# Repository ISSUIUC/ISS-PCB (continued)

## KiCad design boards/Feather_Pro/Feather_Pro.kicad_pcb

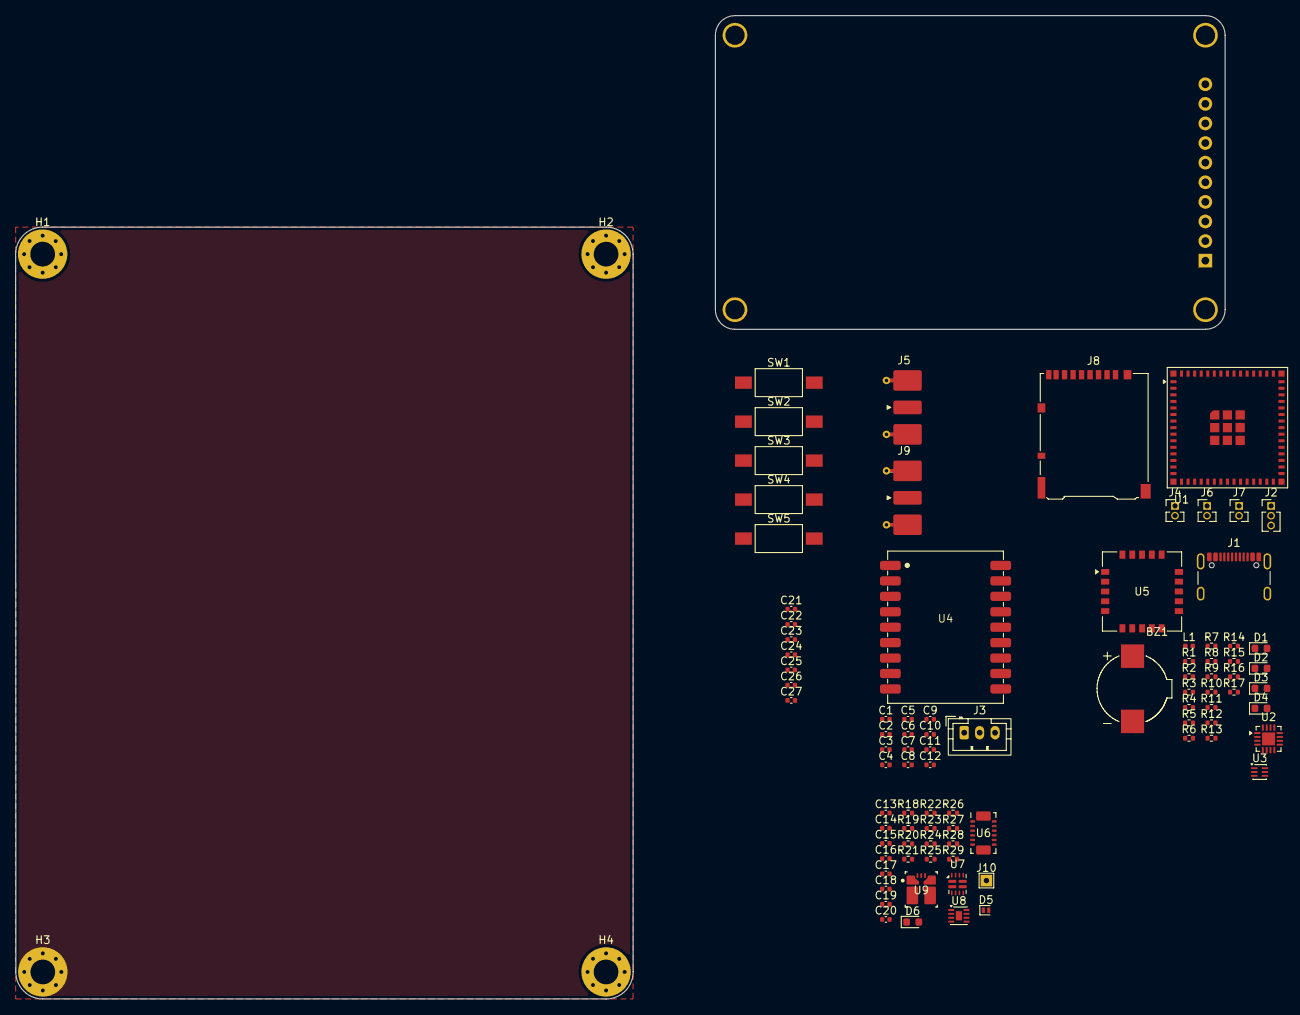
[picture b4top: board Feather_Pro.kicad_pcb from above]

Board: 4 copper layers, 156.7 x 127.4 mm, 93 parts (0 on the bottom side), 76 nets, no tracks yet.

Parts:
BZ1: Buzzer; Buzzer_SMTB-0927-TW-R
C1, C4, C5, C6, C7, C14, C26: 1uF; C_0402_1005Metric
C2, C20: 22uF; C_0402_1005Metric
C3, C13, C21, C22, C23, C24, C25: 0.1uF; C_0402_1005Metric
C8, C10, C17, C27: 100nF; C_0402_1005Metric
C9: 100pF; C_0402_1005Metric
C11: 10uF; C_0402_1005Metric
C12, C18: 10nF; C_0402_1005Metric
C15: 0.1 uF; C_0402_1005Metric
C16: 10Uf; C_0402_1005Metric
C19: 1 uF; C_0402_1005Metric
D1: RED LED; LED_0603_1608Metric
D2: ORANGE LED; LED_0603_1608Metric
D3: GREEN LED; LED_0603_1608Metric
D4: BLUE LED; LED_0603_1608Metric
D5: BAS116L; D_SOD-882
D6: LED; LED_0603_1608Metric
H1, H2, H3, H4: M3; MountingHole_3.2mm_M3_Pad_Via
J1: USB4105-GF-A; USB_C_Receptacle_GCT_USB4105-xx-A_16P_TopMnt_Horizontal
J2: Conn_01x03; PinHeader_1x03_P1.27mm_Vertical
J3: Conn_01x03; JST_PH_B3B-PH-K_1x03_P2.00mm_Vertical
J4, J6, J7: Conn_01x02; PinHeader_1x02_P1.27mm_Vertical
J5, J9: SMA; SMA_Molex_73251-2120_EdgeMount_Horizontal
J8: DM3AT-SF-PEJM5; microSD_HC_Hirose_DM3AT-SF-PEJM5
J10: TestPoint; TestPoint_THTPad_1.5x1.5mm_Drill0.7mm
L1: 330nH; L_0402_1005Metric
R1, R24, R27: 0; R_0402_1005Metric
R2, R17: 100k; R_0402_1005Metric
R3, R4, R5, R6, R29: 470; R_0402_1005Metric
R7, R8: 4.7k; R_0402_1005Metric
R9: 20k; R_0402_1005Metric
R10, R11: 5.1k; R_0402_1005Metric
R12, R13, R14, R15, R16, R22, R26: 10k; R_0402_1005Metric
R18, R20: 16.9k; R_0402_1005Metric
R19, R21: 5k; R_0402_1005Metric
R23: 21.5k; R_0402_1005Metric
R25: 11.8k; R_0402_1005Metric
R28: 10K; R_0402_1005Metric
SW1, SW2, SW3, SW4, SW5: SW_Push; SW_SPST_FSMSM
U1: ESP32-S3-MINI-1U; ESP32-S2-MINI-1U
U2: ADS7138-Q1; WQFN-16-1EP_3x3mm_P0.5mm_EP1.68x1.68mm
U3: ECMF02-2AMX6; ST_UQFN-6L_1.5x1.7mm_P0.5mm
U4: LR2021
U5: E22-400MM22S
U6: INA745x; VQFN-REL0014B
U7: TPS2121; Texas_VQFN-HR-12_2x2.5mm_P0.5mm
U8: MAX17048G+T10; TDFN-8-1EP_2x2mm_P0.5mm_EP0.8x1.2mm
U9: TPSM863253RDXR; QFN-FCMOD-RDX0007A
U10: LCD_2.2_in; Adafruit_2.2_LCD_SCREEN

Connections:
+3V3: C2.1, C3.1, C4.1, C5.1, C7.1, C8.1, C11.1, C12.1, C13.2, C20.1, C26.1, C27.1, J8.4 (VDD), R7.2, R8.2, R9.2, R12.2, R13.2, R14.2, R15.2, R16.2, R17.2, R22.1, R27.1, R28.1, R29.1, U1.3 (3V3), U2.7 (AVDD), U2.10 (DVDD), U4.1 (VCC), U5.1 (VCC), U6.3 (A1), U6.11 (VS), U9.3 (VOUT), U9.7 (FB), U10.9 (VIN)
/ADS_ALERT: U1.17 (IO13), U2.12 (ALERT)
/BOOT_SW: J3.1, U1.4 (IO0)
/BUTTON_CENTER: C25.2, SW5.2, U1.20 (IO16)
/BUTTON_DOWN: C22.1, SW2.1, U1.19 (IO15)
/BUTTON_LEFT: C24.2, SW4.2, U1.22 (IO18)
/BUTTON_RIGHT: C21.1, SW1.1, U1.21 (IO17)
/BUTTON_UP: C23.1, SW3.1, U1.18 (IO14)
/BUZZER: BZ1.1 (+), U2.15 (AIN0/GPIO0)
/D+: J1.A6 (D+), J1.B6 (D+), U3.6 (D+_out)
/D-: J1.A7 (D-), J1.B7 (D-), U3.5 (D-_out)
/E22_BUSY: U1.38 (IO42), U5.11 (BUSY)
/E22_CS: U1.16 (IO12), U5.14 (NSS)
/E22_DIO1: U1.36 (IO40), U5.20 (DIO1)
/E22_DIO3: U1.37 (IO41), U5.18 (DIO3)
/E22_RESET: C10.1, R17.1, U1.34 (IO38), U5.3 (NRST)
/E22_RXEN: U1.35 (IO39), U5.10 (RXEN)
/Feather_Pro_Power/PMUX_GND: C14.1, D5.2 (A), R19.2, R21.2, R23.1, U7.3 (CP2), U7.6 (PR1), U7.9 (ST), U7.12 (GND)
/GPIO_0: J7.1, U2.5 (AIN6/GPIO6)
/GPIO_1: J7.2, U2.6 (AIN7/GPIO7)
/I2C_SCL: J4.2, R8.1, U1.9 (IO5), U2.13 (SCL), U6.6 (SCL), U8.7 (SCL)
/I2C_SDA: J4.1, R7.1, U1.10 (IO6), U2.14 (SDA), U6.5 (SDA), U8.8 (SDA)
/INA_ALERT: R22.2, U1.30 (IO48), U6.10 (ALERT)
/LCD_BL: U1.27 (IO47), U10.1 (BL)
/LCD_CS: U1.15 (IO11), U10.5 (CS)
/LCD_D_C: U1.39 (TXD0), U10.8 (D/C)
/LCD_RST: U1.40 (RXD0), U10.7 (RST)
/LED_BLUE: R6.1, U2.3 (AIN4/GPIO4)
/LED_GREEN: R5.1, U2.2 (AIN3/GPIO3)
/LED_ORANGE: R4.1, U2.1 (ANI2/GPIO2)
/LED_RED: R3.1, U2.16 (AIN1/GPIO1)
/LR2021_ANT: C9.2, U4.9 (ANT)
/LR2021_BUSY: U1.28 (IO33), U4.7 (BUSY)
/LR2021_CS: U1.14 (IO10), U4.6 (~CS)
/LR2021_GPIO7: U1.25 (IO21), U4.17 (DIO7)
/LR2021_GPIO8: U1.5 (IO1), U4.16 (DIO8)
/LR2021_GPIO9: U1.6 (IO2), U4.15 (DIO9)
/LR2021_nRST: U1.8 (IO4), U4.14 (nRST)
/MAX_ALERT: R28.2, U2.4 (AIN5/GPIO5), U8.5 (*ALRT)
/MicroSD_CLK: J8.5 (CLK), U1.31 (IO35)
/MicroSD_CMD: J8.3 (CMD), R14.1, U1.32 (IO36)
/MicroSD_DAT0: J8.7 (DAT0), R13.1, U1.29 (IO34)
/RESET_SW: C6.1, J3.2, R9.1, U1.45 (EN)
/SPI_MISO: J2.3, U1.13 (IO9), U4.3 (MISO), U5.12 (MISO), U10.3 (MISO)
/SPI_MOSI: J2.2, U1.11 (IO7), U4.4 (MOSI), U5.13 (MOSI), U10.4 (MOSI)
/SPI_SCK: J2.1, U1.12 (IO8), U4.5 (SCK), U5.15 (SCK), U10.2 (SCK)
/SYS_POWER: J10.1 (Pin_1_1), U6.13 (VBUS), U6.14 (IS+), U7.1 (OUT), U7.8 (OUT)
/USB_D+: U1.24 (USB_D+), U3.1 (D+_in)
/USB_D-: U1.23 (USB_D-), U3.2 (D-_in)
/USB_POWER: J1.A4 (VBUS), J1.A9 (VBUS), J1.B4 (VBUS), J1.B9 (VBUS), R18.1, U7.7 (IN1)
/VBAT: C15.1, J6.1, R20.1, R24.1, U7.2 (IN2), U8.2 (CELL)
/VREG_IN: C16.1, C17.1, R25.1, U6.7 (IS-), U9.1 (VIN)
GND: BZ1.2 (-), C1.2, C2.2, C3.2, C4.2, C5.2, C6.2, C7.2, C8.2, C10.2, C11.2, C12.2, C13.1, C15.2, C16.2, C17.2, C18.2, C19.2, C20.2, C21.2, C22.2, C23.2, C24.1, C25.1, C26.2, C27.2, D1.1 (K), D2.1 (K), D3.1 (K), D4.1 (K), D5.1 (K), D6.1 (K), J1.A1 (GND), J1.A12 (GND), J1.B1 (GND), J1.B12 (GND), J3.3, J5.2 (Ext), J6.2, J8.6 (VSS), J9.2 (Ext), L1.2, R1.1, R10.2, R11.2, R26.2, SW1.2, SW2.2, SW3.2, SW4.1, SW5.1, U1.1 (GND), U1.2 (GND), U1.42 (GND), U1.43 (GND), U1.46 (GND), U1.47 (GND), U1.48 (GND), U1.49 (GND), U1.50 (GND), U1.51 (GND), U1.52 (GND), U1.53 (GND), U1.54 (GND), U1.55 (GND), U1.56 (GND), U1.57 (GND), U1.58 (GND), U1.59 (GND), U1.60 (GND), U1.61 (GND), U1.62 (GND), U1.63 (GND), U1.64 (GND), U1.65 (GND), U2.9 (GND), U2.17 (EPAD), U3.3 (GND), U4.2 (GND), U4.8 (GND), U4.11 (GND), U4.12 (GND), U4.18 (GND), U5.2 (GND), U5.7 (GND), U5.16 (GND), U6.4 (A0), U6.12 (GND), U8.1 (CTG), U8.4 (GND), U8.6 (QSTRT), U8.9 (EPAD), U9.4 (PGND), U10.10 (GND)
unnamed: D1.2 (A), R3.2
unnamed: D2.2 (A), R4.2
unnamed: D3.2 (A), R5.2
unnamed: D4.2 (A), R6.2
unnamed: D6.2 (A), R29.2
unnamed: J1.A5 (CC1), R10.1
unnamed: J1.B5 (CC2), R11.1
unnamed: C9.1, J5.1 (In)
unnamed: J8.8 (DAT1), R12.1
unnamed: J8.1 (DAT2), R16.1
unnamed: J8.2 (DAT3/CD), R15.1
unnamed: J9.1 (In), L1.1, U5.6 (ANT)
unnamed: R1.2, R2.2, U2.11 (ADDR)
unnamed: C1.1, R2.1, U2.8 (DECAP)
unnamed: U5.9 (TXEN), U5.19 (DIO2)
unnamed: U6.1 (SH+), U6.2 (IN+)
unnamed: U6.8 (SH-), U6.9 (IN-)
unnamed: R23.2, U7.10 (ILM)
unnamed: R18.2, R19.1, U7.5 (OV1)
unnamed: R20.2, R21.1, U7.4 (OV2)
unnamed: C14.2, U7.11 (SS)
unnamed: C19.1, R24.2, R27.2, U8.3 (VDD)
unnamed: C18.1, R25.2, R26.1, U9.6 (EN)

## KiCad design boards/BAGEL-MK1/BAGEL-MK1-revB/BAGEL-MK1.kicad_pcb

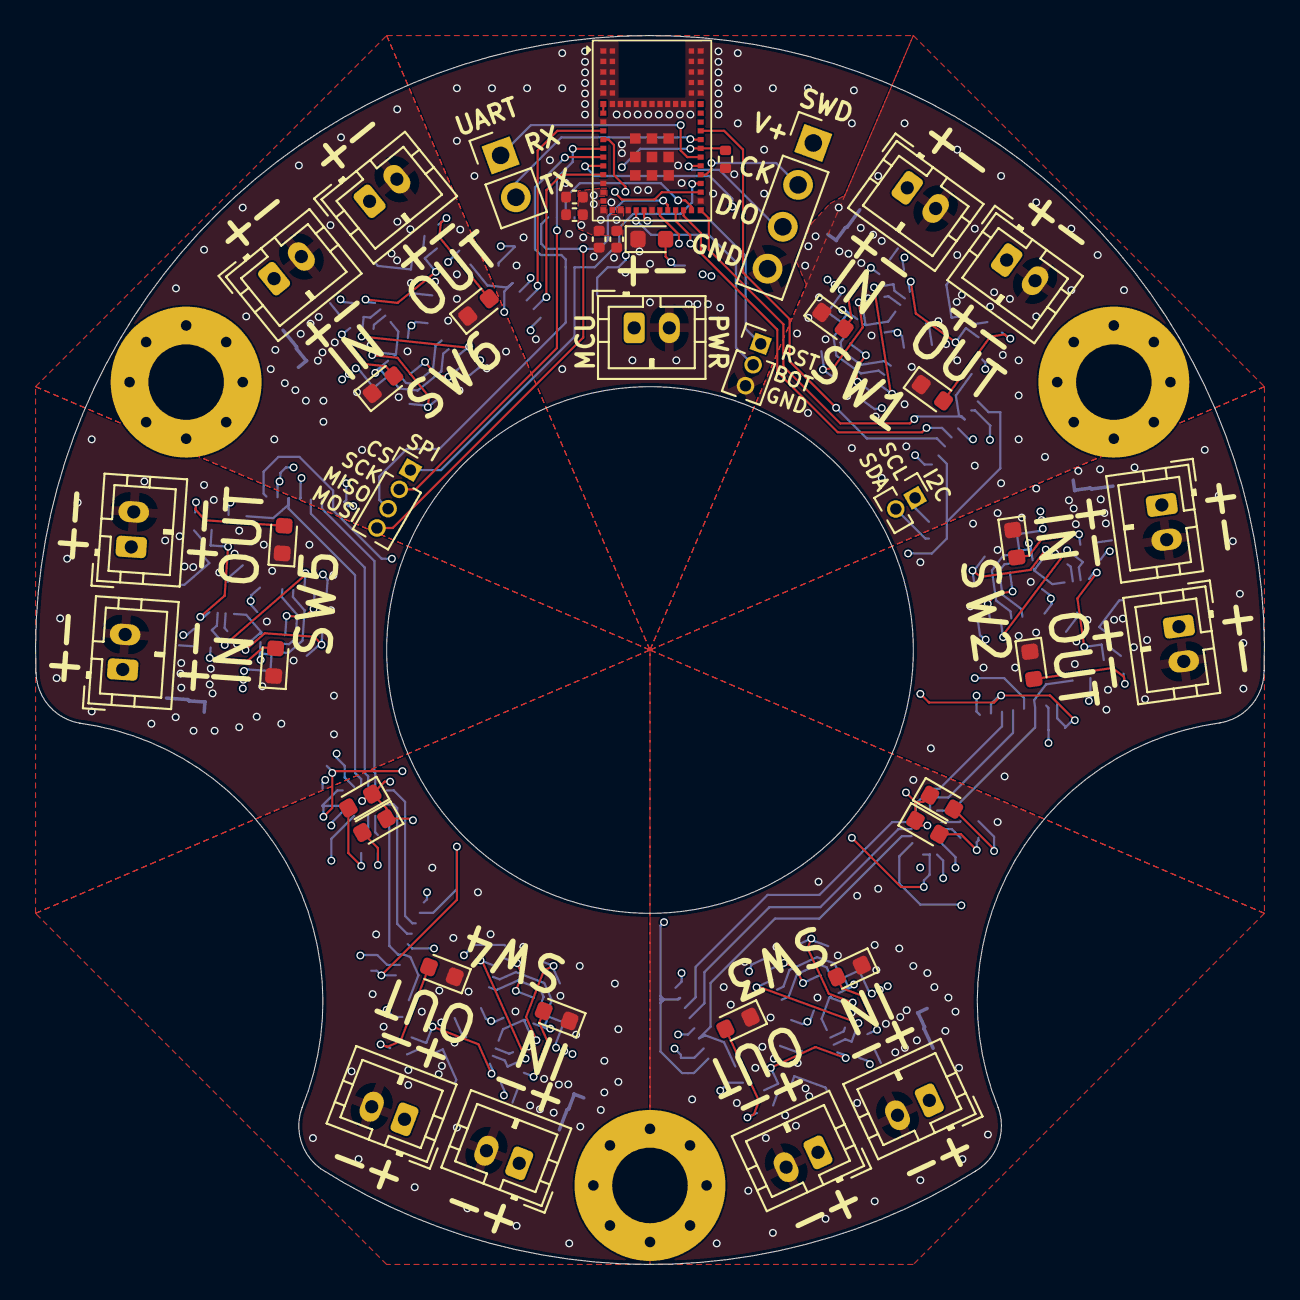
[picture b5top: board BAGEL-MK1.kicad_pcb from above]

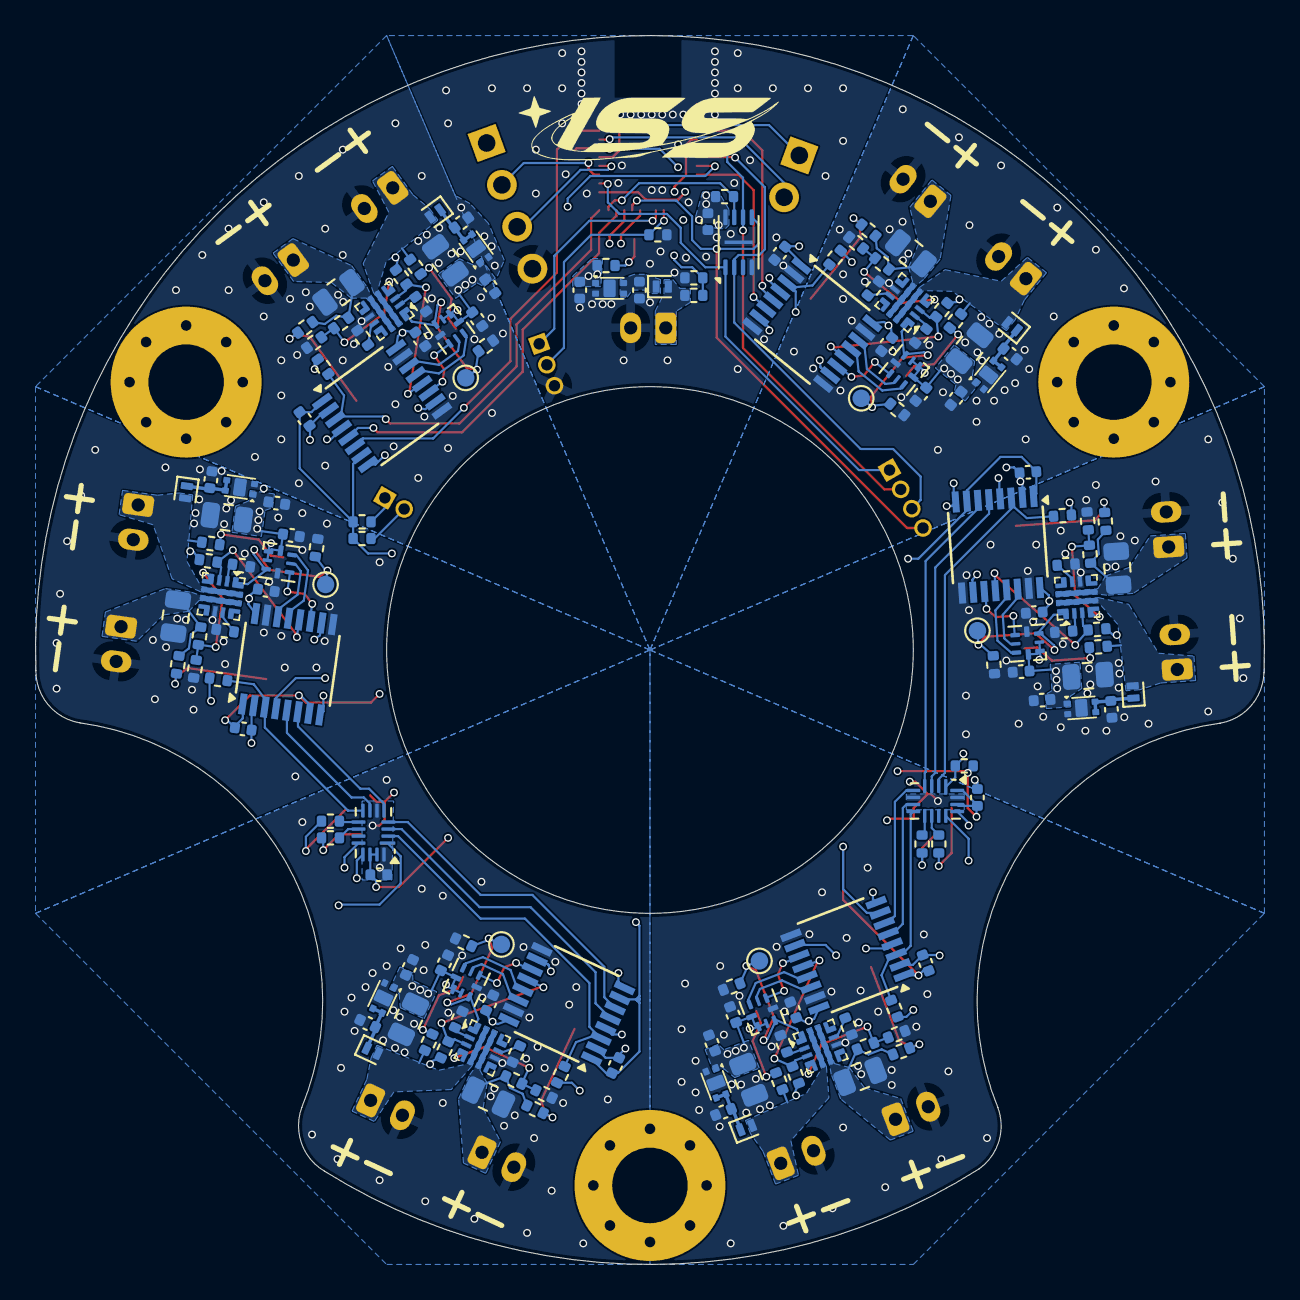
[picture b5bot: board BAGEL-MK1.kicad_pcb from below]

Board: 4 copper layers, 70.0 x 70.0 mm, 198 parts (154 on the bottom side), 138 nets.

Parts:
C101, C103, C104, C105, C108, C109, C201, C202, C203, C301, C302, C303, C401, C402, C403, C501, C502, C503, C601, C602, C603, C701, C702, C703: 100nF; C_0402_1005Metric
C102, C107: 4.7uF; C_0402_1005Metric
C106, C204, C205, C304, C305, C404, C405, C504, C505, C604, C605, C704, C705: 1uF; C_0402_1005Metric
C206, C306, C406, C506, C606, C706: 100uF; C_0805_2012Metric
C207, C307, C407, C507, C607, C707: 22uF; C_0805_2012Metric
D101, D201, D301, D401, D501, D601, D701: SDM05U40CSP-7; D_SOD-882
D102, D103, D202, D302, D402, D502, D602, D702: RED; LED_0603_1608Metric
D104: ORANGE; LED_0603_1608Metric
D105, D203, D303, D403, D503, D603, D703: GREEN; LED_0603_1608Metric
D106: BLUE; LED_0603_1608Metric
H101, H102, H103: MountingHole_Pad; MountingHole_4.3mm_M4_Pad_Via
J101: Conn_01x03; PinHeader_1x03_P1.27mm_Vertical
J102: Conn_01x04; PinHeader_1x04_P2.54mm_Vertical
J103, J201, J203, J301, J303, J401, J403, J501, J503, J601, J603, J701, J703: Conn_01x02; JST_PH_B2B-PH-K_1x02_P2.00mm_Vertical
J104: Conn_01x02; PinHeader_1x02_P2.54mm_Vertical
J105: Conn_01x02; PinHeader_1x02_P1.27mm_Vertical
J106: Conn_01x04; PinHeader_1x04_P1.27mm_Vertical
J202, J302, J402, J502, J602, J702: Conn_01x01; TestPoint_Pad_D1.0mm
R101, R102, R103, R113, R201, R202, R204, R301, R302, R304, R401, R402, R404, R501, R502, R504, R601, R602, R604, R701, R702, R704: 10k; R_0402_1005Metric
R104, R105, R106, R107, R108: 470; R_0402_1005Metric
R109, R112: 4.7k; R_0402_1005Metric
R110, R111: 100k; R_0402_1005Metric
R203, R209, R303, R309, R403, R409, R503, R509, R603, R609, R703, R709: 1k; R_0402_1005Metric
R205, R305, R405, R505, R605, R705: 680; R_0402_1005Metric
R206, R306, R406, R506, R606, R706: 390k; R_0402_1005Metric
R207, R307, R407, R507, R607, R707: 300k; R_0402_1005Metric
R208, R308, R408, R508, R608, R708: 500k; R_0402_1005Metric
U101: W25Q16JLUX; Winbond_USON-8-1EP_3x2mm_P0.5mm_EP0.2x1.6mm
U102: STM32WB1MMC; LGA77_6P5X10_STM
U103, U203, U303, U403, U503, U603, U703: XC6223; Torex_USP-4
U104, U105: TCAL9538; UQFN-16_1.8x2.6mm_P0.4mm
U201, U301, U401, U501, U601, U701: ISO7742; SSOP-16_3.9x4.9mm_P0.635mm
U202, U302, U402, U502, U602, U702: SN74AUP1G74RSER; UQFN-RSE0008A
U204, U304, U404, U504, U604, U704: TPS25947; VQFN-HR-RPW0010A

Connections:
/BLUE_LED: R108.1, U105.10 (P7)
/BOOT: J101.2, R102.2, U102.22 (BOOT0)
/CoinCell_V: D101.2 (A), J103.1, R110.2
/EXP_RESET: R103.1, U102.13 (PA2), U104.1 (~RESET), U105.1 (~RESET)
/FLASH_CS: J106.1, U101.1 (~CS), U102.33 (PB4)
/FLASH_RESET: R101.2, U101.7 (~HOLD/~RESET/IO_{3}), U102.29 (PA7)
/GPIO_Clock: R113.2, U102.37 (PA0), U201.4 (INB), U301.4 (INB), U401.4 (INB), U501.4 (INB), U601.4 (INB), U701.4 (INB)
/GREEN_LED: R107.1, U105.9 (P6)
/I2C_SCL: J105.1, R112.1, U102.27 (PB6), U104.12 (SCL), U105.12 (SCL)
/I2C_SDA: J105.2, R109.1, U102.25 (PB7), U104.13 (SDA), U105.13 (SDA)
/NRST: J101.1, U102.23 (NRST)
/ORANGE_LED: R106.1, U104.10 (P7)
/PG_ISO_1: U102.28 (PA3), U201.5 (OUTC)
/PG_ISO_2: U104.7 (P4), U301.5 (OUTC)
/PG_ISO_3: U104.3 (P1), U401.5 (OUTC)
/PG_ISO_4: U105.7 (P4), U501.5 (OUTC)
/PG_ISO_5: U105.3 (P1), U601.5 (OUTC)
/PG_ISO_6: U102.9 (PA4), U701.5 (OUTC)
/RED_LED: R105.1, U104.9 (P6)
/SPI_MISO: J106.3, U101.2 (DO/IO_{1}), U102.12 (PA6)
/SPI_MOSI: J106.4, U101.5 (DI/IO_{0}), U102.26 (PB5)
/SPI_SCK: J106.2, U101.6 (CLK), U102.11 (PA1)
/SWCLK: J102.2, U102.34 (PA14)
/SWDIO: J102.3, U102.35 (PA13)
/Switch 1/PG: R204.2, U201.12 (INC), U204.3 (PG/AUXOFF)
/Switch 1/Q: J202.1, R202.2, U202.3 (Q), U204.1 (EN/UVLO)
/Switch 1/Reg_V: C201.1, C203.1, C205.1, C206.1, R204.1, U201.10 (EN2), U201.16 (VCC2), U202.1 (~PRE), U202.2 (~CLR), U202.8 (VCC), U203.1 (VOUT)
/Switch 1/SubBatt_GND: C201.2, C203.2, C204.2, C205.2, C206.2, C207.2, D202.1 (K), D203.1 (K), J201.2, J203.2, R202.1, R205.1, R206.2, R208.2, U201.9 (GND2), U201.15 (GND2), U202.4 (GND), U203.2 (VSS), U203.5 (EP), U204.8 (GND)
/Switch 1/SubBatt_V: D201.2 (A), J201.1, R203.1, U204.5 (IN)
/Switch 1/~Q: U201.11 (IND), U202.5 (~Q)
/Switch 2/PG: R304.2, U301.12 (INC), U304.3 (PG/AUXOFF)
/Switch 2/Q: J302.1, R302.2, U302.3 (Q), U304.1 (EN/UVLO)
/Switch 2/Reg_V: C301.1, C303.1, C305.1, C306.1, R304.1, U301.10 (EN2), U301.16 (VCC2), U302.1 (~PRE), U302.2 (~CLR), U302.8 (VCC), U303.1 (VOUT)
/Switch 2/SubBatt_GND: C301.2, C303.2, C304.2, C305.2, C306.2, C307.2, D302.1 (K), D303.1 (K), J301.2, J303.2, R302.1, R305.1, R306.2, R308.2, U301.9 (GND2), U301.15 (GND2), U302.4 (GND), U303.2 (VSS), U303.5 (EP), U304.8 (GND)
/Switch 2/SubBatt_V: D301.2 (A), J301.1, R303.1, U304.5 (IN)
/Switch 2/~Q: U301.11 (IND), U302.5 (~Q)
/Switch 3/PG: R404.2, U401.12 (INC), U404.3 (PG/AUXOFF)
/Switch 3/Q: J402.1, R402.2, U402.3 (Q), U404.1 (EN/UVLO)
/Switch 3/Reg_V: C401.1, C403.1, C405.1, C406.1, R404.1, U401.10 (EN2), U401.16 (VCC2), U402.1 (~PRE), U402.2 (~CLR), U402.8 (VCC), U403.1 (VOUT)
/Switch 3/SubBatt_GND: C401.2, C403.2, C404.2, C405.2, C406.2, C407.2, D402.1 (K), D403.1 (K), J401.2, J403.2, R402.1, R405.1, R406.2, R408.2, U401.9 (GND2), U401.15 (GND2), U402.4 (GND), U403.2 (VSS), U403.5 (EP), U404.8 (GND)
/Switch 3/SubBatt_V: D401.2 (A), J401.1, R403.1, U404.5 (IN)
/Switch 3/~Q: U401.11 (IND), U402.5 (~Q)
/Switch 4/PG: R504.2, U501.12 (INC), U504.3 (PG/AUXOFF)
/Switch 4/Q: J502.1, R502.2, U502.3 (Q), U504.1 (EN/UVLO)
/Switch 4/Reg_V: C501.1, C503.1, C505.1, C506.1, R504.1, U501.10 (EN2), U501.16 (VCC2), U502.1 (~PRE), U502.2 (~CLR), U502.8 (VCC), U503.1 (VOUT)
/Switch 4/SubBatt_GND: C501.2, C503.2, C504.2, C505.2, C506.2, C507.2, D502.1 (K), D503.1 (K), J501.2, J503.2, R502.1, R505.1, R506.2, R508.2, U501.9 (GND2), U501.15 (GND2), U502.4 (GND), U503.2 (VSS), U503.5 (EP), U504.8 (GND)
/Switch 4/SubBatt_V: D501.2 (A), J501.1, R503.1, U504.5 (IN)
/Switch 4/~Q: U501.11 (IND), U502.5 (~Q)
/Switch 5/PG: R604.2, U601.12 (INC), U604.3 (PG/AUXOFF)
/Switch 5/Q: J602.1, R602.2, U602.3 (Q), U604.1 (EN/UVLO)
/Switch 5/Reg_V: C601.1, C603.1, C605.1, C606.1, R604.1, U601.10 (EN2), U601.16 (VCC2), U602.1 (~PRE), U602.2 (~CLR), U602.8 (VCC), U603.1 (VOUT)
/Switch 5/SubBatt_GND: C601.2, C603.2, C604.2, C605.2, C606.2, C607.2, D602.1 (K), D603.1 (K), J601.2, J603.2, R602.1, R605.1, R606.2, R608.2, U601.9 (GND2), U601.15 (GND2), U602.4 (GND), U603.2 (VSS), U603.5 (EP), U604.8 (GND)
/Switch 5/SubBatt_V: D601.2 (A), J601.1, R603.1, U604.5 (IN)
/Switch 5/~Q: U601.11 (IND), U602.5 (~Q)
/Switch 6/PG: R704.2, U701.12 (INC), U704.3 (PG/AUXOFF)
/Switch 6/Q: J702.1, R702.2, U702.3 (Q), U704.1 (EN/UVLO)
/Switch 6/Reg_V: C701.1, C703.1, C705.1, C706.1, R704.1, U701.10 (EN2), U701.16 (VCC2), U702.1 (~PRE), U702.2 (~CLR), U702.8 (VCC), U703.1 (VOUT)
/Switch 6/SubBatt_GND: C701.2, C703.2, C704.2, C705.2, C706.2, C707.2, D702.1 (K), D703.1 (K), J701.2, J703.2, R702.1, R705.1, R706.2, R708.2, U701.9 (GND2), U701.15 (GND2), U702.4 (GND), U703.2 (VSS), U703.5 (EP), U704.8 (GND)
/Switch 6/SubBatt_V: D701.2 (A), J701.1, R703.1, U704.5 (IN)
/Switch 6/~Q: U701.11 (IND), U702.5 (~Q)
/Switch_1: R201.1, U102.30 (PA12), U201.3 (INA)
/Switch_2: R301.1, U104.8 (P5), U301.3 (INA)
/Switch_3: R401.1, U104.2 (P0), U401.3 (INA)
/Switch_4: R501.1, U105.8 (P5), U501.3 (INA)
/Switch_5: R601.1, U105.2 (P0), U601.3 (INA)
/Switch_6: R701.1, U102.32 (PA11), U701.3 (INA)
/UART_RX: J104.1, U102.36 (PA10)
/UART_TX: J104.2, U102.38 (PA9)
/V_SENSE: R110.1, R111.2, U102.10 (PA8)
/~Q_ISO_1: U102.39 (PA5), U201.6 (OUTD)
/~Q_ISO_2: U104.5 (P3), U301.6 (OUTD)
/~Q_ISO_3: U104.4 (P2), U401.6 (OUTD)
/~Q_ISO_4: U105.5 (P3), U501.6 (OUTD)
/~Q_ISO_5: U105.4 (P2), U601.6 (OUTD)
/~Q_ISO_6: U102.14 (PB8), U701.6 (OUTD)
MCU_GND: C101.2, C102.2, C103.2, C104.2, C105.2, C106.2, C107.2, C108.2, C109.2, C202.2, C302.2, C402.2, C502.2, C602.2, C702.2, D102.1 (K), D103.1 (K), D104.1 (K), D105.1 (K), D106.1 (K), J101.3, J102.4, J103.2, R102.1, R111.1, R113.1, R201.2, R301.2, R401.2, R501.2, R601.2, R701.2, U101.4 (GND), U101.9 (EP), U102.1 (VSS), U102.2 (VSS), U102.3 (VSS), U102.4 (VSS), U102.5 (VSSRF), U102.8 (VSSRF), U102.15 (VSS), U102.17 (VSS), U102.19 (VSS), U102.21 (VSSSMPS), U102.24 (VSS), U102.31 (VSS), U102.43 (VSS), U102.44 (VSS), U102.45 (VSS), U102.46 (VSS), U102.47 (VSS), U102.48 (VSS), U102.49 (VSS), U102.50 (VSS), U102.51 (VSS), U102.52 (VSS), U102.53 (VSS), U102.54 (VSS), U102.55 (VSS), U102.56 (VSS), U102.57 (VSS), U102.58 (VSS), U102.59 (VSS), U102.60 (VSS), U102.61 (VSS), U102.62 (VSS), U102.63 (VSS), U102.64 (VSS), U102.65 (VSS), U102.66 (VSS), U102.67 (VSS), U102.68 (VSS), U102.69 (VSS), U102.70 (VSS), U102.71 (VSS), U102.72 (VSS), U102.73 (VSS), U102.74 (VSS), U102.75 (VSS), U102.76 (VSS), U102.77 (VSS), U103.2 (VSS), U103.5 (EP), U104.6 (GND), U104.16 (A1), U105.6 (GND), U105.15 (A0), U201.2 (GND1), U201.8 (GND1), U301.2 (GND1), U301.8 (GND1), U401.2 (GND1), U401.8 (GND1), U501.2 (GND1), U501.8 (GND1), U601.2 (GND1), U601.8 (GND1), U701.2 (GND1), U701.8 (GND1)
MCU_V: C101.1, C102.1, C103.1, C104.1, C105.1, C107.1, C108.1, C109.1, C202.1, C302.1, C402.1, C502.1, C602.1, C702.1, J102.1, R101.1, R103.2, R104.2, R109.2, R112.2, U101.8 (VCC), U102.16 (VDDA), U102.18 (VBAT), U102.20 (VDDSMPS), U103.1 (VOUT), U104.14 (VCC), U104.15 (A0), U105.14 (VCC), U105.16 (A1), U201.1 (VCC1), U201.7 (EN1), U301.1 (VCC1), U301.7 (EN1), U401.1 (VCC1), U401.7 (EN1), U501.1 (VCC1), U501.7 (EN1), U601.1 (VCC1), U601.7 (EN1), U701.1 (VCC1), U701.7 (EN1)
unnamed: C106.1, D101.1 (K), U103.3 (CE), U103.4 (VIN)
unnamed: D102.2 (A), R104.1
unnamed: D103.2 (A), R105.2
unnamed: D104.2 (A), R106.2
unnamed: D105.2 (A), R107.2
unnamed: D106.2 (A), R108.2
unnamed: C204.1, D201.1 (K), U203.3 (CE), U203.4 (VIN)
unnamed: D202.2 (A), R203.2
unnamed: D203.2 (A), R209.2
unnamed: C304.1, D301.1 (K), U303.3 (CE), U303.4 (VIN)
unnamed: D302.2 (A), R303.2
unnamed: D303.2 (A), R309.2
unnamed: C404.1, D401.1 (K), U403.3 (CE), U403.4 (VIN)
unnamed: D402.2 (A), R403.2
unnamed: D403.2 (A), R409.2
unnamed: C504.1, D501.1 (K), U503.3 (CE), U503.4 (VIN)
unnamed: D502.2 (A), R503.2
unnamed: D503.2 (A), R509.2
unnamed: C604.1, D601.1 (K), U603.3 (CE), U603.4 (VIN)
unnamed: D602.2 (A), R603.2
unnamed: D603.2 (A), R609.2
unnamed: C704.1, D701.1 (K), U703.3 (CE), U703.4 (VIN)
unnamed: D702.2 (A), R703.2
unnamed: D703.2 (A), R709.2
unnamed: C207.1, J203.1, R207.1, R209.1, U204.6 (OUT)
unnamed: C307.1, J303.1, R307.1, R309.1, U304.6 (OUT)
unnamed: C407.1, J403.1, R407.1, R409.1, U404.6 (OUT)
unnamed: C507.1, J503.1, R507.1, R509.1, U504.6 (OUT)
unnamed: C607.1, J603.1, R607.1, R609.1, U604.6 (OUT)
unnamed: C707.1, J703.1, R707.1, R709.1, U704.6 (OUT)
unnamed: U102.6 (ANT_IN), U102.7 (ANT_OUT)
unnamed: U201.14 (OUTA), U202.6 (D)
unnamed: U201.13 (OUTB), U202.7 (CLK)
unnamed: R205.2, U204.9 (ILM)
unnamed: R206.1, U204.2 (OVLO/OVCSEL)
unnamed: R207.2, R208.1, U204.4 (PGTH/NFLT)
unnamed: U301.14 (OUTA), U302.6 (D)
unnamed: U301.13 (OUTB), U302.7 (CLK)
unnamed: R305.2, U304.9 (ILM)
unnamed: R306.1, U304.2 (OVLO/OVCSEL)
unnamed: R307.2, R308.1, U304.4 (PGTH/NFLT)
unnamed: U401.14 (OUTA), U402.6 (D)
unnamed: U401.13 (OUTB), U402.7 (CLK)
unnamed: R405.2, U404.9 (ILM)
unnamed: R406.1, U404.2 (OVLO/OVCSEL)
unnamed: R407.2, R408.1, U404.4 (PGTH/NFLT)
unnamed: U501.14 (OUTA), U502.6 (D)
unnamed: U501.13 (OUTB), U502.7 (CLK)
unnamed: R505.2, U504.9 (ILM)
unnamed: R506.1, U504.2 (OVLO/OVCSEL)
unnamed: R507.2, R508.1, U504.4 (PGTH/NFLT)
unnamed: U601.14 (OUTA), U602.6 (D)
unnamed: U601.13 (OUTB), U602.7 (CLK)
unnamed: R605.2, U604.9 (ILM)
unnamed: R606.1, U604.2 (OVLO/OVCSEL)
unnamed: R607.2, R608.1, U604.4 (PGTH/NFLT)
unnamed: U701.14 (OUTA), U702.6 (D)
unnamed: U701.13 (OUTB), U702.7 (CLK)
unnamed: R705.2, U704.9 (ILM)
unnamed: R706.1, U704.2 (OVLO/OVCSEL)
unnamed: R707.2, R708.1, U704.4 (PGTH/NFLT)

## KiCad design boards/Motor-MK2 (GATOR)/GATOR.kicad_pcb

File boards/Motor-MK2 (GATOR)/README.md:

# Motorboard MK2 - GATOR

G - Grounded 

A - Arieal 

T - Tracker 

O - for Our 

R - Rocket 

# MK2

MK2 now includes an onboard LoRa reciever and GPS, removing the need for another MIDAS to act as a ground station.
It now also includes Qwiic connectors for additional I2C support and an IMU for orientation correction if needed.

# MK1

Starting off the year as just a concept, the Motor Board has taken shape as an impressive new piece of the MIDAS ecosystem. Unofficially known as “Spinny Antenna Motor” (SAM) Board, the project serves as a method of control for the team’s SAM Turret antenna tracker, which aims to automatically track the rocket’s position during flight and maintain optimal antenna orientation to get the best possible range for MIDAS telemetry. In addition to cementing MIDAS’s role as an important part of our team’s ground operations, the Motor Board has served as a testbed for WiFi as a new way of board-to-board communication.

Read more about MotorBoard, MIDAS and the surrounding avionics systems in the [MIDAS MK2 Report](https://uofi.box.com/s/k0ad6ryhxbzwpdwt33lxyxuxpivv3qhj).

# Schematics

Printable PDF schematics and layouts for MotorBoard can be found in the PDFs and images folders.

# Photos

## MK1

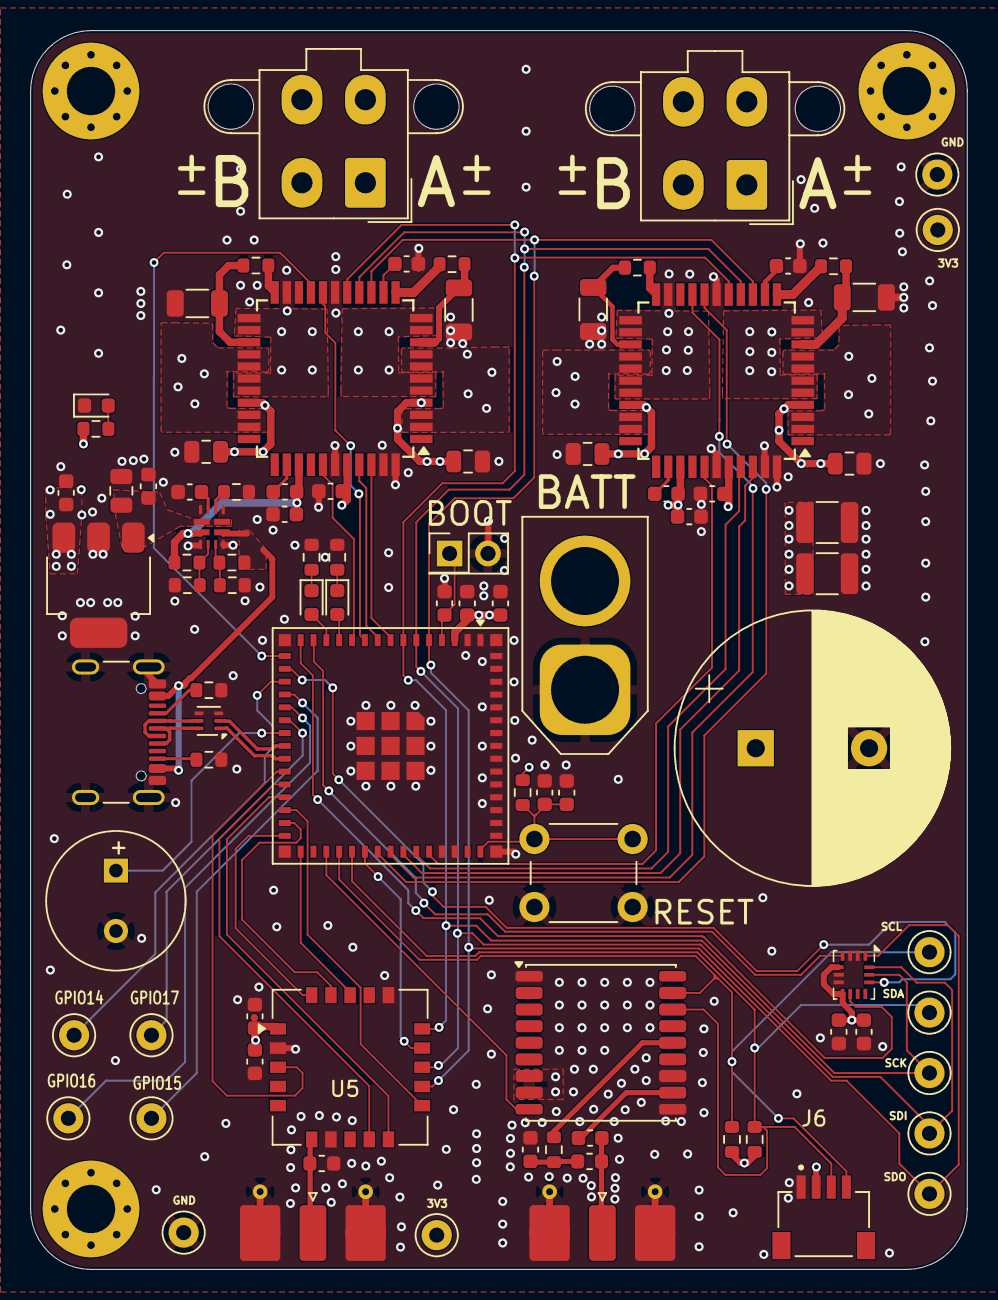
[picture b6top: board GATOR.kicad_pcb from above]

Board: 4 copper layers, 62.0 x 82.0 mm, 92 parts (0 on the bottom side), 79 nets.

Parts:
BZ1: AT-0927-TT-6-R; Buzzer_AT-0927-TT-6-R
C1, C3, C8, C10, C14, C16, C18, C25: 100nF; C_0603_1608Metric
C2, C12: 220nF; C_0603_1608Metric
C4, C5, C17, C19, C26: 10uF; C_0805_2012Metric
C6, C27: 22uF; C_0603_1608Metric
C7, C20: 470nF; C_0603_1608Metric
C9: 1200uF; CP_Radial_D18.0mm_P7.50mm
C11, C23: 1uF; C_0603_1608Metric
C13, C15: 100uF; C_1210_3225Metric
C21: 10uF; C_0603_1608Metric
C22, C402: 10nF; C_0603_1608Metric
C102, C103: 0.1uF; C_0603_1608Metric
C403: 47pF; C_0603_1608Metric
D1, D2: LED; LED_0603_1608Metric
D3: RED LED; LED_0603_1608Metric
H1, H2, H3: MountingHole; MountingHole_3.2mm_M3_Pad_Via
J1: USB_C_Receptacle_USB2.0_16P; USB_C_Receptacle_GCT_USB4105-xx-A_16P_TopMnt_Horizontal
J2, J4: Conn_01x04; Molex_Mini-Fit_Jr_5566-04A2_2x02_P4.20mm_Vertical
J3: XT60; AMASS_XT60-M_1x02_P7.20mm_Vertical
J5, J401: SMA; SMA_Molex_73251-2120_EdgeMount_Horizontal
J6: PRT-14417; Qwiic_4_pin_horizontal
L1: 330nH; L_0603_1608Metric
L401: 27nH; L_0603_1608Metric
R1, R2: 5.1k; R_0603_1608Metric
R3, R4, R8, R9, R401: 10; R_0603_1608Metric
R5, R6, R10, R11: 0.075; R_1206_3216Metric
R7: 100k; R_0603_1608Metric
R12: 23.7k; R_0603_1608Metric
R13: 5k; R_0603_1608Metric
R14: 30k; R_0603_1608Metric
R15: 1k; R_0603_1608Metric
R16, R17, R21: 470; R_0603_1608Metric
R18: 20k; R_0603_1608Metric
R19, R20: 4.7k; R_0603_1608Metric
SW1: SW_Push; PinHeader_2x01_P2.54mm_Vertical
SW2: SW_Push; SW_PUSH_6mm
TP3V3-1, TP3V3-2: 3V3; TestPoint_Keystone_5000-5004_Miniature
TP-GND-1, TP-GND-2: GND; TestPoint_Keystone_5000-5004_Miniature
TP-IO14-1: GPIO14; TestPoint_Keystone_5000-5004_Miniature
TP-IO15-2: GPIO15; TestPoint_Keystone_5000-5004_Miniature
TP-IO16-3: GPIO16; TestPoint_Keystone_5000-5004_Miniature
TP-IO17-4: GPIO17; TestPoint_Keystone_5000-5004_Miniature
TPSCK1: SCK; TestPoint_Keystone_5000-5004_Miniature
TPSCL1: I2C_SCL; TestPoint_Keystone_5000-5004_Miniature
TPSDA1: I2C_SDA; TestPoint_Keystone_5000-5004_Miniature
TPSDI1: SDI; TestPoint_Keystone_5000-5004_Miniature
TPSDO1: SDO; TestPoint_Keystone_5000-5004_Miniature
U1, U4: TMC2660C; TQFP-44_10x10mm_P0.8mm
U2: ESP32-S3-MINI-1U; ESP32-S2-MINI-1U
U3: ECMF02-2AMX6; ST_UQFN-6L_1.5x1.7mm_P0.5mm
U5: E22-400MM22S
U6: TPS2121; VQFN-HR-RUX0012A
U8: TLE42744; SOT-223
U102: LSM6DSLTR; Bosch_LGA-14_3x2.5mm_P0.5mm
U403: MAX-M10S; ublox_MAX

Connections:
+3V3: C1.2, C6.2, C8.2, C10.2, C21.1, C22.1, C27.1, C102.1, C103.1, J6.2, R7.1, R19.2, R20.2, R21.1, TP3V3-1.1, TP3V3-2.1, U1.40 (VCC_IO), U2.3 (3V3), U4.40 (VCC_IO), U5.1 (VCC), U8.3 (Q), U102.5 (VDDIO), U102.8 (VDD), U403.7 (VCC_IO), U403.8 (VCC)
/BUZZER: BZ1.1 (-), U2.22 (IO18)
/D+: J1.A6 (D+), J1.B6 (D+), U3.6 (D+_out)
/D-: J1.A7 (D-), J1.B7 (D-), U3.5 (D-_out)
/DIR_0: U1.41 (DIR), U2.9 (IO5)
/DIR_1: U2.40 (RXD0), U4.41 (DIR)
/E22_BUSY: U2.28 (IO33), U5.11 (BUSY)
/E22_DI01: U2.30 (IO48), U5.20 (DIO1)
/E22_DI02: U2.29 (IO34), U5.19 (DIO2)
/E22_DI03: U2.31 (IO35), U5.18 (DIO3)
/E22_RESET: U2.25 (IO21), U5.3 (NRST)
/GPIO14: TP-IO14-1.1, U2.18 (IO14)
/GPIO15: TP-IO15-2.1, U2.19 (IO15)
/GPIO16: TP-IO16-3.1, U2.20 (IO16)
/GPIO17: TP-IO17-4.1, U2.21 (IO17)
/I2C_SCL: J6.4, R19.1, TPSCL1.1, U2.34 (IO38), U403.17 (SCL)
/I2C_SDA: J6.3, R20.1, TPSDA1.1, U2.35 (IO39), U403.16 (SDA)
/LED_1: D1.2 (A), U2.12 (IO8)
/LED_2: D2.2 (A), U2.13 (IO9)
/LORA_CS: U2.36 (IO40), U5.14 (NSS)
/LSM6DSLTR_INT1: U2.14 (IO10), U102.4 (INT1)
/LSM6DSLTR_INT2: U2.15 (IO11), U102.9 (INT2)
/LSM6DSL_CS: U2.17 (IO13), U102.12 (CS)
/MAX_RESET: U2.33 (IO37), U403.9 (~RESET)
/RXEN: U2.27 (IO47), U5.10 (RXEN)
/SCK: TPSCK1.1, U1.16 (SCK), U2.7 (IO3), U4.16 (SCK), U5.15 (SCK), U102.13 (SCL)
/SDI: TPSDI1.1, U1.15 (SDI), U2.6 (IO2), U4.15 (SDI), U5.13 (MOSI), U102.14 (SDA)
/SDO: TPSDO1.1, U1.14 (SDO), U2.5 (IO1), U4.14 (SDO), U5.12 (MISO), U102.1 (SDO/SA0)
/SG_TST_0: U1.38 (SG_TST), U2.11 (IO7)
/SG_TST_1: U2.41 (IO45), U4.38 (SG_TST)
/STEP_0: U1.42 (STEP), U2.8 (IO4)
/STEP_1: U2.39 (TXD0), U4.42 (STEP)
/SYS_Power: C25.1, C26.1, U6.1 (OUT), U6.8 (OUT), U8.1 (I)
/TXEN: U2.26 (IO26), U5.9 (TXEN)
/USB_POWER: J1.A4 (VBUS), J1.A9 (VBUS), J1.B4 (VBUS), J1.B9 (VBUS), R12.1, U6.7 (IN1)
/VBAT: C2.1, C3.1, C4.1, C5.1, C9.1, C12.1, C13.1, C14.1, C15.1, C17.1, C19.1, J3.2, R14.1, U1.4 (VSA), U1.30 (VSB), U1.36 (VS), U4.4 (VSA), U4.30 (VSB), U4.36 (VS), U6.2 (IN2)
/~CS_0: U1.18 (~CS), U2.10 (IO6)
/~CS_1: U2.37 (IO41), U4.18 (~CS)
/~EN_0: U1.19 (~EN), U2.16 (IO12)
/~EN_1: U2.38 (IO42), U4.19 (~EN)
BOOT_SW: C16.1, SW1.1, U2.4 (IO0)
GND: BZ1.2 (+), C1.1, C3.2, C4.2, C5.2, C6.1, C7.2, C8.1, C9.2, C10.1, C11.2, C13.2, C14.2, C15.2, C16.2, C17.2, C18.2, C19.2, C20.2, C21.2, C22.2, C23.2, C25.2, C26.2, C27.2, C102.2, C103.2, C402.2, D3.1 (K), J1.A1 (GND), J1.A12 (GND), J1.B1 (GND), J1.B12 (GND), J1.S1 (SHIELD), J3.1, J5.2 (Ext), J6.1, J401.2 (Ext), L1.2, R1.2, R2.2, R5.2, R6.2, R10.2, R11.2, R13.2, R15.2, R16.2, R17.2, R18.2, SW1.2, SW2.2, TP-GND-1.1, TP-GND-2.1, U1.17 (GND), U1.21 (CLK), U1.39 (GND), U1.43 (TST_MODE), U1.44 (GND), U2.1 (GND), U2.2 (GND), U2.42 (GND), U2.43 (GND), U2.46 (GND), U2.47 (GND), U2.48 (GND), U2.49 (GND), U2.50 (GND), U2.51 (GND), U2.52 (GND), U2.53 (GND), U2.54 (GND), U2.55 (GND), U2.56 (GND), U2.57 (GND), U2.58 (GND), U2.59 (GND), U2.60 (GND), U2.61 (GND), U2.62 (GND), U2.63 (GND), U2.64 (GND), U2.65 (GND), U3.3 (GND), U3.4 (NC), U4.17 (GND), U4.21 (CLK), U4.39 (GND), U4.43 (TST_MODE), U4.44 (GND), U5.2 (GND), U5.7 (GND), U5.16 (GND), U6.3 (CP2), U6.6 (PR1), U6.9 (ST), U6.12 (GND), U8.2 (GND), U8.4 (GND), U102.2 (SDx), U102.3 (SCx), U102.6 (GND), U102.7 (GND), U403.1 (GND), U403.10 (GND), U403.12 (GND)
unnamed: C402.1, L401.2, R401.2
unnamed: D1.1 (K), R16.1
unnamed: D2.1 (K), R17.1
unnamed: D3.2 (A), R21.2
unnamed: J1.A5 (CC1), R1.1
unnamed: J1.B5 (CC2), R2.1
unnamed: J2.1, U1.5 (OA2), U1.6 (OA2), U1.10 (OA2), U1.11 (OA2)
unnamed: J2.2, U1.23 (OB2), U1.24 (OB2), U1.28 (OB2), U1.29 (OB2)
unnamed: J2.3, U1.2 (OA1), U1.3 (OA1), U1.7 (OA1), U1.8 (OA1)
unnamed: J2.4, U1.26 (OB1), U1.27 (OB1), U1.31 (OB1), U1.32 (OB1)
unnamed: J4.1, U4.5 (OA2), U4.6 (OA2), U4.10 (OA2), U4.11 (OA2)
unnamed: J4.2, U4.23 (OB2), U4.24 (OB2), U4.28 (OB2), U4.29 (OB2)
unnamed: J4.3, U4.2 (OA1), U4.3 (OA1), U4.7 (OA1), U4.8 (OA1)
unnamed: J4.4, U4.26 (OB1), U4.27 (OB1), U4.31 (OB1), U4.32 (OB1)
unnamed: J5.1 (In), L1.1, U5.6 (ANT)
unnamed: C403.1, J401.1 (In), L401.1
unnamed: C7.1, U1.13 (5VOUT)
unnamed: R3.2, R5.1, U1.9 (BRA)
unnamed: R4.2, R6.1, U1.25 (BRB)
unnamed: R3.1, U1.12 (SRA)
unnamed: R4.1, U1.22 (SRB)
unnamed: C2.2, U1.35 (VHS)
unnamed: C20.1, U4.13 (5VOUT)
unnamed: R8.2, R10.1, U4.9 (BRA)
unnamed: R9.2, R11.1, U4.25 (BRB)
unnamed: R8.1, U4.12 (SRA)
unnamed: R9.1, U4.22 (SRB)
unnamed: C12.2, U4.35 (VHS)
unnamed: R18.1, U6.10 (ILM)
unnamed: R12.2, R13.1, U6.5 (OV1)
unnamed: R14.2, R15.1, U6.4 (OV2)
unnamed: C23.1, U6.11 (SS)
unnamed: C403.2, U403.11 (RF_IN)
unnamed: R401.1, U403.14 (VCC_RF)
RESET_SW: C11.1, C18.1, R7.2, SW2.1, U2.45 (EN)
USB+: U2.24 (IO20), U3.1 (D+_in)
USB-: U2.23 (IO19), U3.2 (D-_in)
